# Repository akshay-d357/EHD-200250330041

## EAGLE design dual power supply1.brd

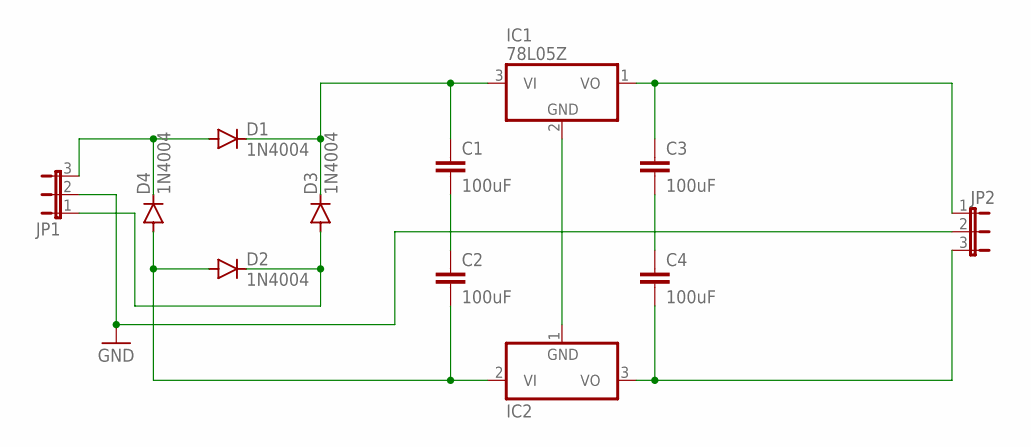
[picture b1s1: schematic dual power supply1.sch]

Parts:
C1, C2, C3, C4: 100uF; C2.5-2
D1, D2, D3, D4: 1N4004; DO41-10
IC1: 78L05Z; TO92
IC2: 7905L; TO92
JP1, JP2: JP2E; JP2

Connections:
GND: JP1.2, JP2.2
unnamed: D1.A, D4.C, JP1.3
unnamed: C1.1, D1.C, D3.C, IC1.3 (VI)
unnamed: D2.C, D3.A, JP1.1
unnamed: C2.2, D2.A, D4.A, IC2.2 (VI)
unnamed: IC1.2 (GND), IC2.1 (GND)
unnamed: C3.1, IC1.1 (VO), JP2.1
unnamed: C4.2, IC2.3 (VO), JP2.3
unnamed: C1.2, C2.1
unnamed: C3.2, C4.1

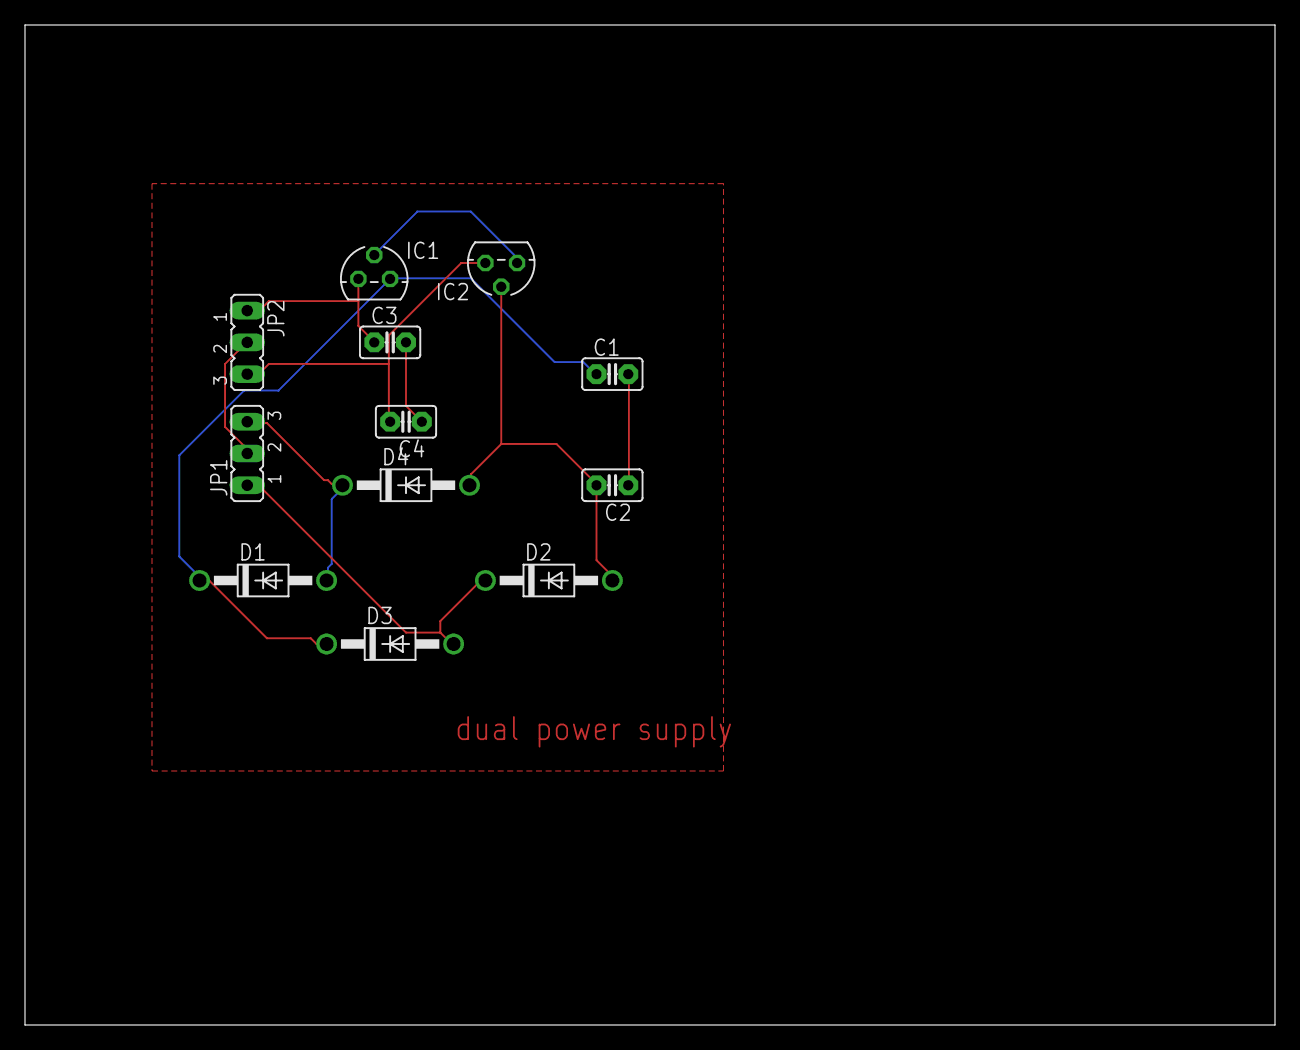
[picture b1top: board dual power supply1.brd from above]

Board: 2 copper layers, 100.0 x 80.0 mm, 12 parts (0 on the bottom side), 10 nets.

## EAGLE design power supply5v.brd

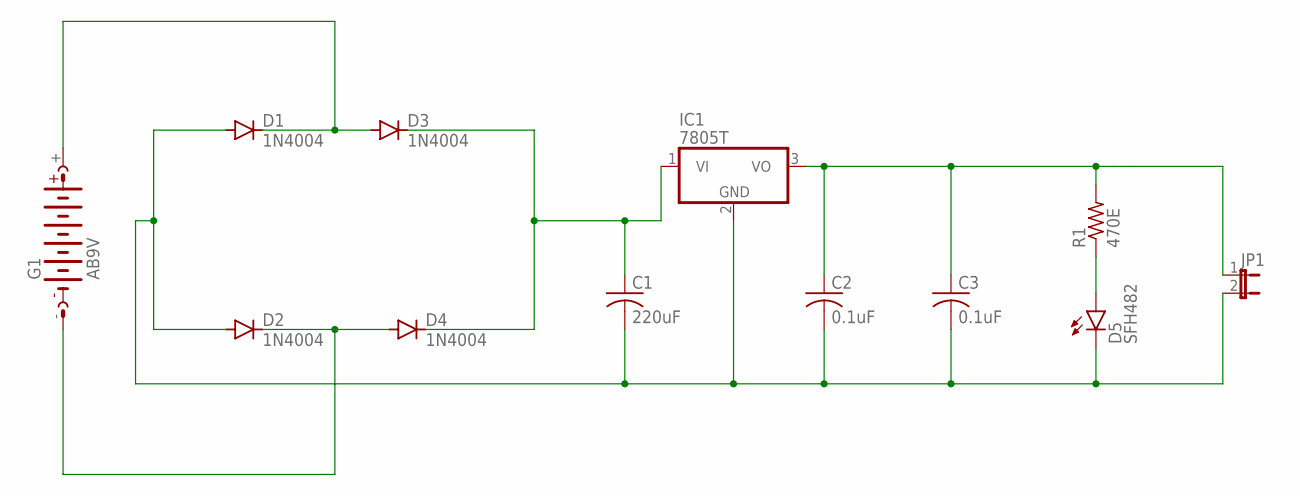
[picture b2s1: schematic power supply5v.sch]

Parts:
C1: 220uF; C050-024X044
C2, C3: 0.1uF; C050-024X044
D1, D2, D3, D4: 1N4004; DO41-10
D5: SFH482
G1: AB9V
IC1: 7805T; TO220H
JP1: JP1E; JP1
R1: 470E; 0204/7

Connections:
unnamed: C1.2, C2.2, C3.2, D1.A, D2.A, D5.K (C), IC1.2 (GND), JP1.2
unnamed: D1.C, D3.A, G1.+
unnamed: D2.C, D4.A, G1.-
unnamed: C1.1, D3.C, D4.C, IC1.1 (VI)
unnamed: C2.1, C3.1, IC1.3 (VO), JP1.1, R1.2
unnamed: D5.A, R1.1

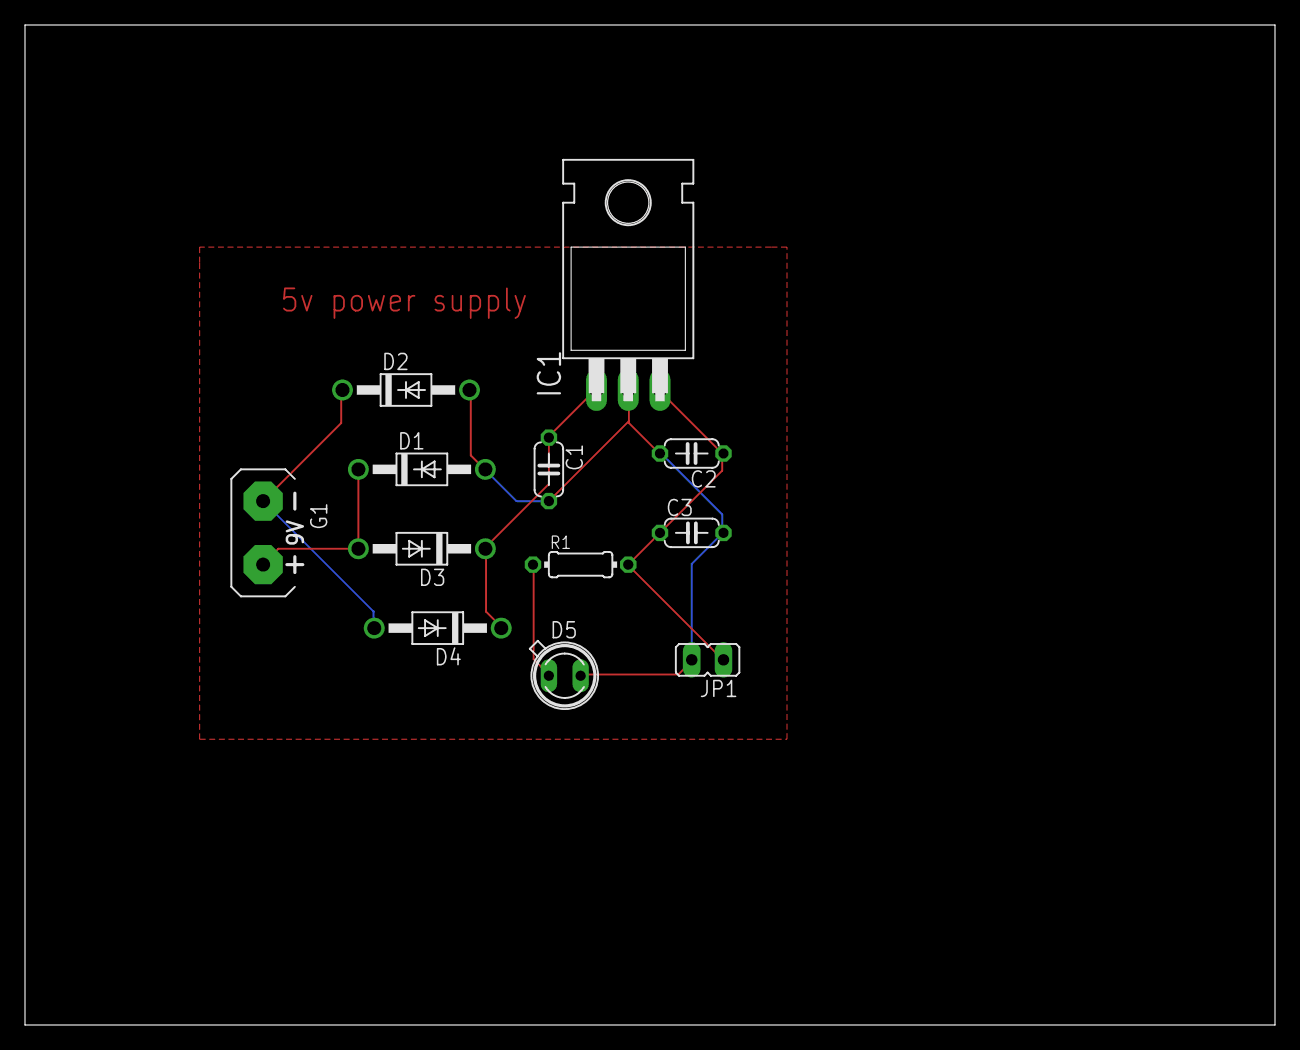
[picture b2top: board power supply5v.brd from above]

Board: 2 copper layers, 100.0 x 80.0 mm, 12 parts (0 on the bottom side), 6 nets.

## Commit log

2020-10-03 Delete power supply5v.brd
    Delete1
